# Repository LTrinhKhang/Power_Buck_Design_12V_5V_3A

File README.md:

# TPS5430 12V → 5V 3A Buck Converter  
## 2-Layer Power PCB Design (EMI-Optimized)

---

## 🎯 Project Objective

Design and validate a manufacturable 2-layer PCB buck converter delivering:

- 12V input  
- Regulated 5V output  
- 3A continuous load  

Focus areas:

- Power loop optimization  
- EMI mitigation  
- Current density control  
- Manufacturability (DFM clean)  
- Ground return integrity  

This project demonstrates practical power PCB layout competency beyond schematic-level design.

---

# 📄 Schematic

Controller: TPS5430DDA (500 kHz, non-synchronous buck)

Key Components:

- 10 µH shielded inductor (≥4.5A Isat)
- SS54 Schottky diode
- 47µF + 22µF input capacitors
- 100µF + 10µF output capacitors
- Feedback: 309k / 100k → 5.0V output

---

# ⚙️ Power Design Calculations

### Inductor Ripple Current

For:

Vin = 12V  
Vout = 5V  
fSW = 500 kHz  
L = 10 µH  

Inductor ripple current:

ΔIL ≈ 0.58A  

Peak inductor current:

Ipeak ≈ 3.3A  

Inductor selected with ≥4.5A saturation current for margin.

---

### Output Voltage

TPS5430 reference voltage: 1.221V  

Using:

R1 = 309k  
R2 = 100k  

Vout ≈ 5.0V  

---

# 🔥 Power Stage Layout Strategy

## Hot Loop Control

The critical high di/dt loop:

VIN → SW → DIODE → CIN return  

Design actions:

- Loop area minimized
- SW trace length ≈ 3–4 mm
- Input capacitor placed adjacent to VIN and PGND
- PGND kept compact and low impedance

Reduced loop area → reduced parasitic inductance → lower radiated EMI.

---

## Bottom Ground Plane

- Continuous ground plane
- Short return paths
- Low impedance reference
- Improved thermal spreading

No signal traces routed under the SW node region.

---

# 📐 Current Density & Trace Width Justification

Target load: 3A DC  

Using IPC-2152 estimation (1 oz copper, 20°C rise):

Required width ≈ 1.0 mm  

Implemented width = 1.5 mm  

Benefits:

- Reduced voltage drop
- Lower copper temperature rise
- Better transient stability
- Improved reliability margin

---

# ⚡ EMI Mitigation Techniques

Switch node dv/dt and di/dt controlled by:

- Minimal SW copper area
- No routing under SW
- Tight input loop
- Shielded inductor selection
- Controlled ground return path

Increasing SW loop length significantly increases loop inductance and radiated EMI.

This layout prioritizes magnetic loop reduction over aesthetic symmetry.

---

# 🧩 3D Rendering

## Top View

## Bottom View

---

# 🛠️ DRC & Manufacturability

## DRC Validation

Final DRC status:

- No clearance violations
- Drill ≥ 0.30 mm
- Proper thermal relief
- Adequate copper spacing at switching node
- Gerber clean before fabrication

Designed for compatibility with standard fabrication services.

---

# 📊 Design Trade-offs

2-layer stackup chosen intentionally to:

- Demonstrate return path control without internal planes
- Control EMI using layout discipline rather than stackup advantage
- Maintain low manufacturing cost

4-layer version would improve:

- EMI suppression
- Controlled impedance
- Thermal performance

---

# 🧠 Engineering Competencies Demonstrated

- Buck converter power stage calculation  
- Loop inductance awareness  
- EMI-conscious routing  
- Ground strategy implementation  
- IPC-based current sizing  
- DRC-driven manufacturability validation  

---

# 🚀 Future Work

- Efficiency measurement validation  
- Load transient response testing  
- Thermal imaging analysis  
- Optional RC snubber optimization  
- 4-layer redesign comparison study  

---

# License

MIT License

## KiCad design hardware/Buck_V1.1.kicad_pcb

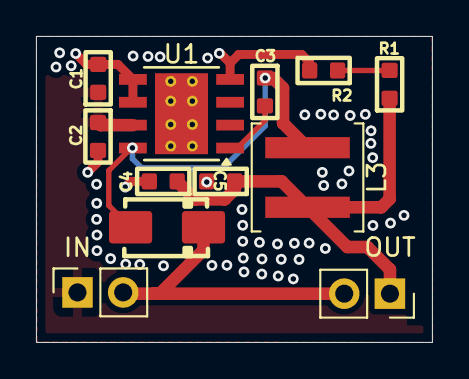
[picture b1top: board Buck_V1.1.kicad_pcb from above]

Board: 2 copper layers, 22.0 x 17.0 mm, 12 parts (0 on the bottom side), 6 nets.

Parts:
C1, C3, C5: 10uF; C_0603
C2, C4: 1uF; C_0603
D3: D_Schottky_Small; Package-Diode-D_SMA
IN: Conn_01x02_Socket; PinSocket_1x02_P2.54mm_Vertical
L3: 15uH; L_Coilcraft_XAL5030-XXX
OUT: Conn_01x02_Socket; PinSocket_1x02_P2.54mm_Vertical
R1: 316; R_0603
R2: 100K; R_0603
U1: TPS5430DDA; TI_SO-PowerPAD-8_ThermalVias

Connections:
/Vin: C1.1, C2.1, IN.1, U1.7 (VIN)
/Vout: C4.1, C5.1, L3.2, OUT.1, R1.1
GND: C1.2, C2.2, C4.2, C5.2, D3.2 (A), IN.2, OUT.2, R2.2, U1.4 (VSENSE), U1.5 (EN), U1.6 (GND)
unnamed: C3.1, D3.1 (K), L3.1, U1.8 (PH)
unnamed: R1.2, R2.1
unnamed: C3.2, U1.1 (BOOT)

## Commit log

2026-02-25 Initial release: TPS5430 12V-5V 3A Buck Converter
2026-02-25 Fix: Rename image and update DCR check screenshot
